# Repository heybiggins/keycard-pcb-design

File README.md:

# keycard-pcb-design

## I built the PCB for this keyboard using:

https://docs.ergogen.xyz/

https://www.kicad.org/

https://jlcpcb.com/

## I followed these guides:

https://flatfootfox.com/ergogen-introduction/

https://youtu.be/UKfeJrRIcxw (Ben Vallack)

https://kbd.news/The-Japanese-duplex-matrix-1391.html

## I wrote about the experience:

https://heybiggins.com/keycard/

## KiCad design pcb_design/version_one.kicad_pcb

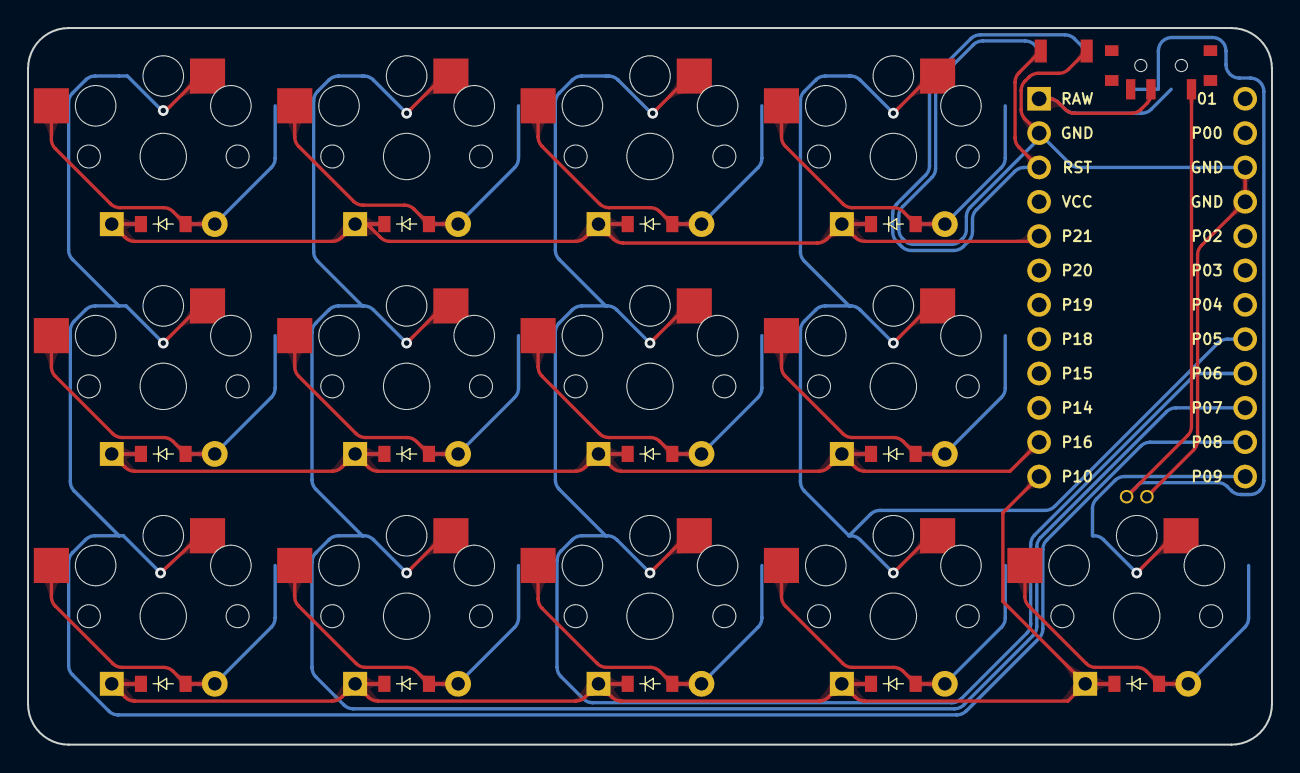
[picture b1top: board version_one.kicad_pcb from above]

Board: 2 copper layers, 92.0 x 53.0 mm, 27 parts (0 on the bottom side), 22 nets.

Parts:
D1, D2, D3, D4, D5, D6, D7, D8, D9, D10, D11, D12, D13: ComboDiode
MCU1: ProMicro
S1, S2, S3, S4, S5, S6, S7, S8, S9, S10, S11, S12, S13: PG1350

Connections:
GND: MCU1.2, MCU1.15, MCU1.16
P5: MCU1.20, S10.1, S11.1, S12.1
P6: MCU1.21, S7.1, S8.1, S9.1
P7: MCU1.22, S4.1, S5.1, S6.1
P8: MCU1.23, S1.1, S2.1, S3.1
P9: MCU1.24, S13.1
P10: D1.1, D4.1, D7.1, D10.1, D13.1, MCU1.12
P16: D2.1, D5.1, D8.1, D11.1, MCU1.11
P21: D3.1, D6.1, D9.1, D12.1, MCU1.5
index_bottom: D10.2, S10.2
index_home: D11.2, S11.2
index_top: D12.2, S12.2
middle_bottom: D7.2, S7.2
middle_home: D8.2, S8.2
middle_top: D9.2, S9.2
pinky_bottom: D1.2, S1.2
pinky_home: D2.2, S2.2
pinky_top: D3.2, S3.2
ring_bottom: D4.2, S4.2
ring_home: D5.2, S5.2
ring_top: D6.2, S6.2
thumb_bottom: D13.2, S13.2

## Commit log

2024-02-25 Create footprints
2024-02-25 Create outlines
2024-02-25 Create card_gerbers
2024-02-25 add kicad files
2024-02-25 add footprints
2024-02-25 add ergogen outlines
